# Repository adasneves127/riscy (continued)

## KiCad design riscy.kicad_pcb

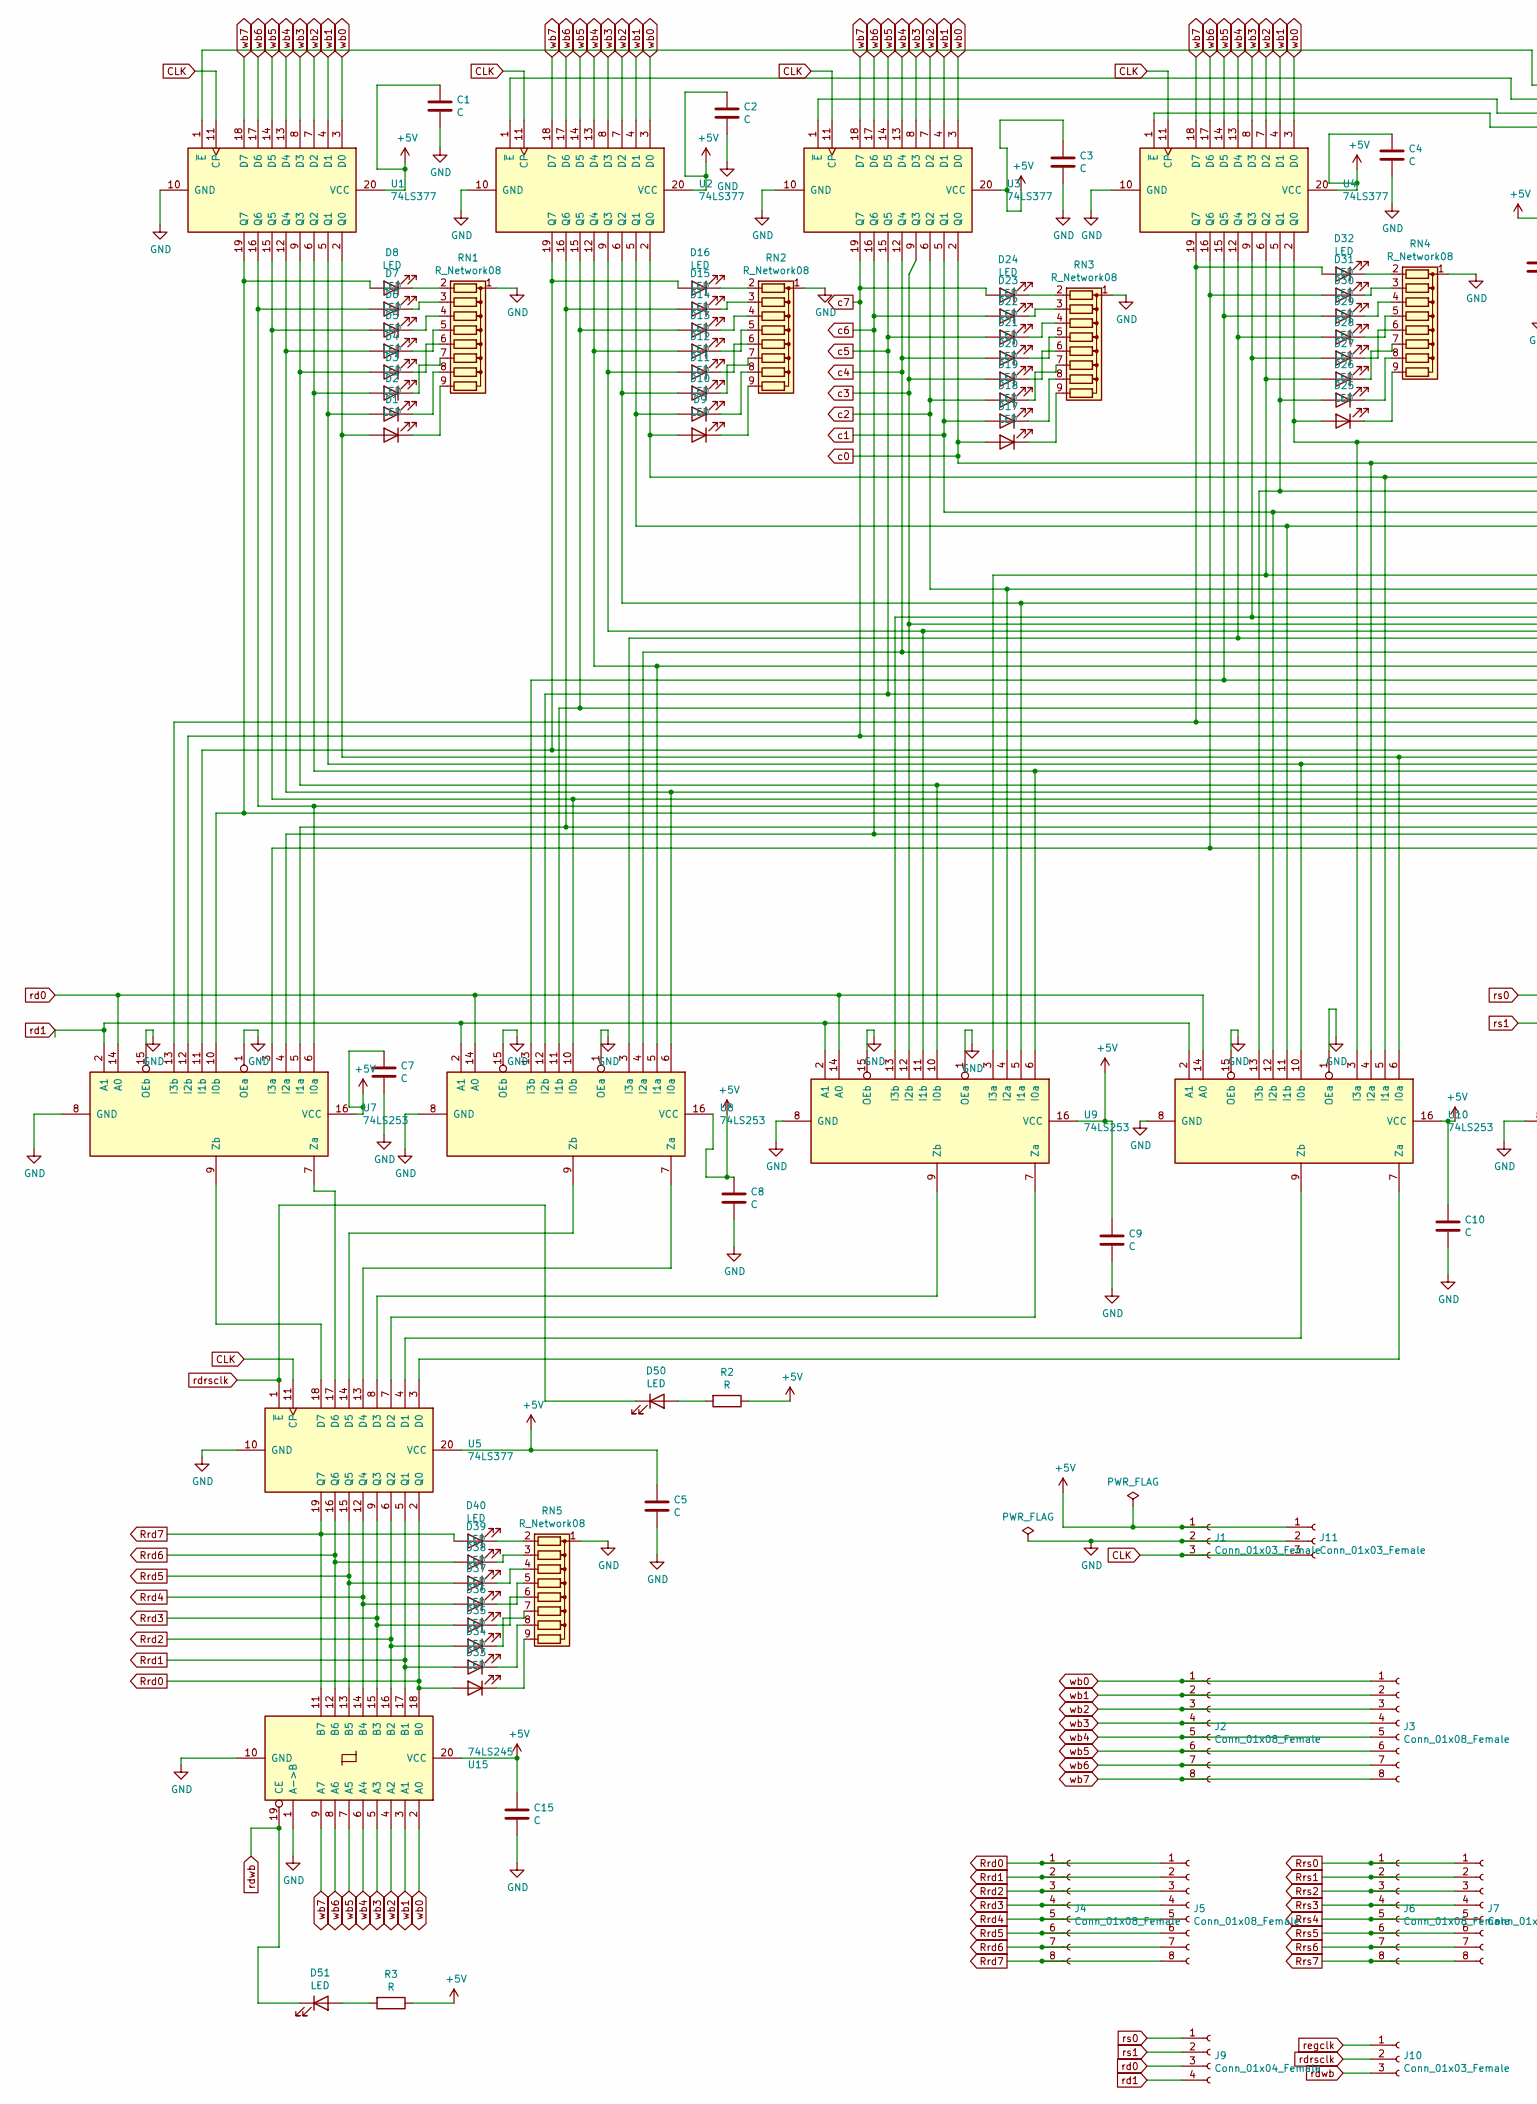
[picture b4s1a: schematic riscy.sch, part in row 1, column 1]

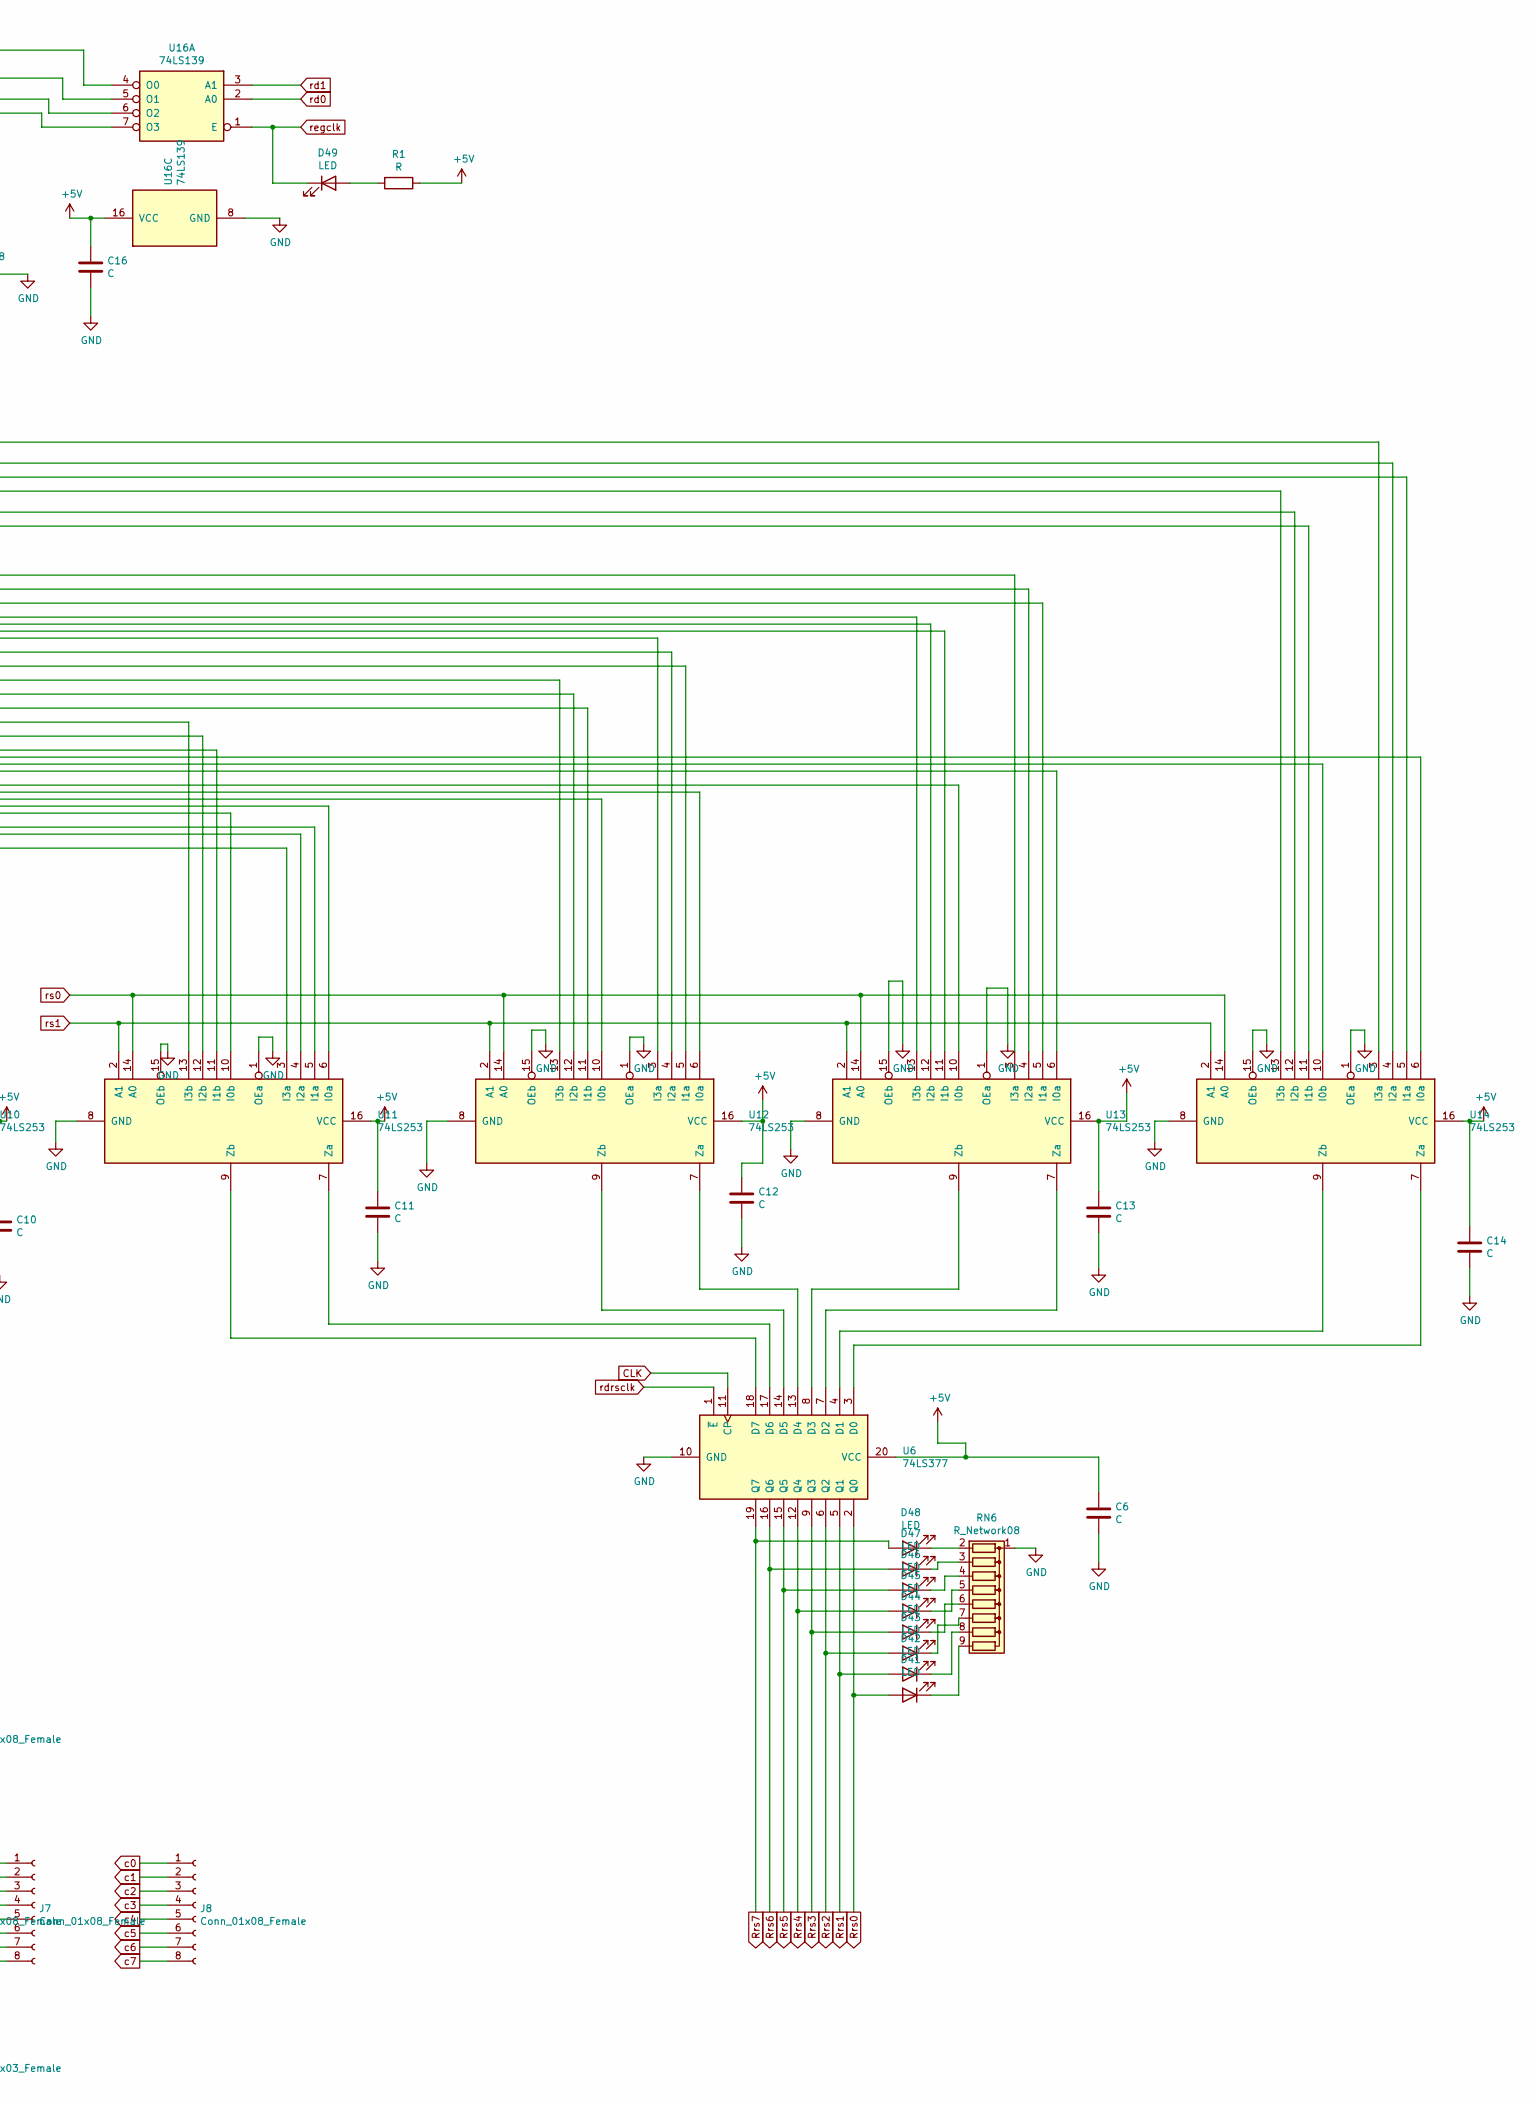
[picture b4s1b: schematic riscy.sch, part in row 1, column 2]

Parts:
C1, C2, C3, C4, C5, C6, C7, C8, C9, C10, C11, C12, C13, C14, C15, C16: C; C_Disc_D3.0mm_W2.0mm_P2.50mm
D1, D2, D3, D4, D5, D6, D7, D8, D9, D10, D11, D12, D13, D14, D15, D16, D17, D18, D19, D20, D21, D22, D23, D24, D25, D26, D27, D28, D29, D30, D31, D32, D33, D34, D35, D36, D37, D38, D39, D40, D41, D42, D43, D44, D45, D46, D47, D48, D49, D50, D51: LED; LED_D5.0mm
J1, J10, J11: Conn_01x03_Female; PinHeader_1x03_P2.54mm_Vertical
J2, J3, J4, J5, J6, J7, J8: Conn_01x08_Female; PinHeader_1x08_P2.54mm_Vertical
J9: Conn_01x04_Female; PinHeader_1x04_P2.54mm_Vertical
R1, R2, R3: R; R_Axial_DIN0204_L3.6mm_D1.6mm_P2.54mm_Vertical
RN1, RN2, RN3, RN4, RN5, RN6: R_Network08; R_Array_SIP9
U1, U2, U3, U4, U5, U6: 74LS377; DIP-20_W7.62mm
U7, U8, U9, U10, U11, U12, U13, U14: 74LS253; DIP-16_W7.62mm
U15: 74LS245; DIP-20_W7.62mm
U16: 74LS139; DIP-16_W7.62mm

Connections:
+5V: C1.1, C2.1, C3.1, C4.1, C5.1, C6.1, C7.1, C8.1, C9.1, C10.1, C11.1, C12.1, C13.1, C14.1, C15.1, C16.1, J1.1, J11.1, R1.1, R2.1, R3.1, U1.20 (VCC), U2.20 (VCC), U3.20 (VCC), U4.20 (VCC), U5.20 (VCC), U6.20 (VCC), U7.16 (VCC), U8.16 (VCC), U9.16 (VCC), U10.16 (VCC), U11.16 (VCC), U12.16 (VCC), U13.16 (VCC), U14.16 (VCC), U15.20 (VCC), U16.16 (VCC)
CLK: J1.3, J11.3, U1.11 (CP), U2.11 (CP), U3.11 (CP), U4.11 (CP), U5.11 (CP), U6.11 (CP)
GND: C1.2, C2.2, C3.2, C4.2, C5.2, C6.2, C7.2, C8.2, C9.2, C10.2, C11.2, C12.2, C13.2, C14.2, C15.2, C16.2, J1.2, J11.2, RN1.1 (common), RN2.1 (common), RN3.1 (common), RN4.1 (common), RN5.1 (common), RN6.1 (common), U1.10 (GND), U2.10 (GND), U3.10 (GND), U4.10 (GND), U5.10 (GND), U6.10 (GND), U7.1 (OEa), U7.8 (GND), U7.15 (OEb), U8.1 (OEa), U8.8 (GND), U8.15 (OEb), U9.1 (OEa), U9.8 (GND), U9.15 (OEb), U10.1 (OEa), U10.8 (GND), U10.15 (OEb), U11.1 (OEa), U11.8 (GND), U11.15 (OEb), U12.1 (OEa), U12.8 (GND), U12.15 (OEb), U13.1 (OEa), U13.8 (GND), U13.15 (OEb), U14.1 (OEa), U14.8 (GND), U14.15 (OEb), U15.1 (A->B), U15.10 (GND), U16.8 (GND)
unnamed: D1.1 (K), RN1.9 (R8)
unnamed: D1.2 (A), U1.2 (Q0), U10.6 (I0a), U14.6 (I0a)
unnamed: D2.1 (K), RN1.8 (R7)
unnamed: D2.2 (A), U1.5 (Q1), U10.10 (I0b), U14.10 (I0b)
unnamed: D3.1 (K), RN1.7 (R6)
unnamed: D3.2 (A), U1.6 (Q2), U9.6 (I0a), U13.6 (I0a)
unnamed: D4.1 (K), RN1.6 (R5)
unnamed: D4.2 (A), U1.9 (Q3), U9.10 (I0b), U13.10 (I0b)
unnamed: D5.1 (K), RN1.5 (R4)
unnamed: D5.2 (A), U1.12 (Q4), U8.6 (I0a), U12.6 (I0a)
unnamed: D6.1 (K), RN1.4 (R3)
unnamed: D6.2 (A), U1.15 (Q5), U8.10 (I0b), U12.10 (I0b)
unnamed: D7.1 (K), RN1.3 (R2)
unnamed: D7.2 (A), U1.16 (Q6), U7.6 (I0a), U11.6 (I0a)
unnamed: D8.1 (K), RN1.2 (R1)
unnamed: D8.2 (A), U1.19 (Q7), U7.10 (I0b), U11.10 (I0b)
unnamed: D9.1 (K), RN2.9 (R8)
unnamed: D9.2 (A), U2.2 (Q0), U10.5 (I1a), U14.5 (I1a)
unnamed: D10.1 (K), RN2.8 (R7)
unnamed: D10.2 (A), U2.5 (Q1), U10.11 (I1b), U14.11 (I1b)
unnamed: D11.1 (K), RN2.7 (R6)
unnamed: D11.2 (A), U2.6 (Q2), U9.5 (I1a), U13.5 (I1a)
unnamed: D12.1 (K), RN2.6 (R5)
unnamed: D12.2 (A), U2.9 (Q3), U9.11 (I1b), U13.11 (I1b)
unnamed: D13.1 (K), RN2.5 (R4)
unnamed: D13.2 (A), U2.12 (Q4), U8.5 (I1a), U12.5 (I1a)
unnamed: D14.1 (K), RN2.4 (R3)
unnamed: D14.2 (A), U2.15 (Q5), U8.11 (I1b), U12.11 (I1b)
unnamed: D15.1 (K), RN2.3 (R2)
unnamed: D15.2 (A), U2.16 (Q6), U7.5 (I1a), U11.5 (I1a)
unnamed: D16.1 (K), RN2.2 (R1)
unnamed: D16.2 (A), U2.19 (Q7), U7.11 (I1b), U11.11 (I1b)
unnamed: D17.1 (K), RN3.9 (R8)
unnamed: D18.1 (K), RN3.8 (R7)
unnamed: D19.1 (K), RN3.7 (R6)
unnamed: D20.1 (K), RN3.6 (R5)
unnamed: D21.1 (K), RN3.5 (R4)
unnamed: D22.1 (K), RN3.4 (R3)
unnamed: D23.1 (K), RN3.3 (R2)
unnamed: D24.1 (K), RN3.2 (R1)
unnamed: D25.1 (K), RN4.9 (R8)
unnamed: D25.2 (A), U4.2 (Q0), U10.3 (I3a), U14.3 (I3a)
unnamed: D26.1 (K), RN4.8 (R7)
unnamed: D26.2 (A), U4.5 (Q1), U10.13 (I3b), U14.13 (I3b)
unnamed: D27.1 (K), RN4.7 (R6)
unnamed: D27.2 (A), U4.6 (Q2), U9.3 (I3a), U13.3 (I3a)
unnamed: D28.1 (K), RN4.6 (R5)
unnamed: D28.2 (A), U4.9 (Q3), U9.13 (I3b), U13.13 (I3b)
unnamed: D29.1 (K), RN4.5 (R4)
unnamed: D29.2 (A), U4.12 (Q4), U8.3 (I3a), U12.3 (I3a)
unnamed: D30.1 (K), RN4.4 (R3)
unnamed: D30.2 (A), U4.15 (Q5), U8.13 (I3b), U12.13 (I3b)
unnamed: D31.1 (K), RN4.3 (R2)
unnamed: D31.2 (A), U4.16 (Q6), U7.3 (I3a), U11.3 (I3a)
unnamed: D32.1 (K), RN4.2 (R1)
unnamed: D32.2 (A), U4.19 (Q7), U7.13 (I3b), U11.13 (I3b)
unnamed: D33.1 (K), RN5.9 (R8)
unnamed: D34.1 (K), RN5.8 (R7)
unnamed: D35.1 (K), RN5.7 (R6)
unnamed: D36.1 (K), RN5.6 (R5)
unnamed: D37.1 (K), RN5.5 (R4)
unnamed: D38.1 (K), RN5.4 (R3)
unnamed: D39.1 (K), RN5.3 (R2)
unnamed: D40.1 (K), RN5.2 (R1)
unnamed: D41.1 (K), RN6.9 (R8)
unnamed: D42.1 (K), RN6.8 (R7)
unnamed: D43.1 (K), RN6.7 (R6)
unnamed: D44.1 (K), RN6.6 (R5)
unnamed: D45.1 (K), RN6.5 (R4)
unnamed: D46.1 (K), RN6.4 (R3)
unnamed: D47.1 (K), RN6.3 (R2)
unnamed: D48.1 (K), RN6.2 (R1)
unnamed: D49.2 (A), R1.2
unnamed: D50.2 (A), R2.2
unnamed: D51.2 (A), R3.2
unnamed: U1.1 (~E), U16.4 (O0)
unnamed: U5.7 (D2), U9.7 (Za)
unnamed: U5.8 (D3), U9.9 (Zb)
unnamed: U5.13 (D4), U8.7 (Za)
unnamed: U5.14 (D5), U8.9 (Zb)
unnamed: U5.17 (D6), U7.7 (Za)
unnamed: U5.18 (D7), U7.9 (Zb)
unnamed: U5.3 (D0), U10.7 (Za)
unnamed: U5.4 (D1), U10.9 (Zb)
unnamed: U6.17 (D6), U11.7 (Za)
unnamed: U6.18 (D7), U11.9 (Zb)
unnamed: U6.13 (D4), U12.7 (Za)
unnamed: U6.14 (D5), U12.9 (Zb)
unnamed: U6.7 (D2), U13.7 (Za)
unnamed: U6.8 (D3), U13.9 (Zb)
unnamed: U6.3 (D0), U14.7 (Za)
unnamed: U6.4 (D1), U14.9 (Zb)
unnamed: U2.1 (~E), U16.5 (O1)
unnamed: U3.1 (~E), U16.6 (O2)
unnamed: U4.1 (~E), U16.7 (O3)
Rrd0: D33.2 (A), J4.1, J5.1, U5.2 (Q0), U15.18 (B0)
Rrd1: D34.2 (A), J4.2, J5.2, U5.5 (Q1), U15.17 (B1)
Rrd2: D35.2 (A), J4.3, J5.3, U5.6 (Q2), U15.16 (B2)
Rrd3: D36.2 (A), J4.4, J5.4, U5.9 (Q3), U15.15 (B3)
Rrd4: D37.2 (A), J4.5, J5.5, U5.12 (Q4), U15.14 (B4)
Rrd5: D38.2 (A), J4.6, J5.6, U5.15 (Q5), U15.13 (B5)
Rrd6: D39.2 (A), J4.7, J5.7, U5.16 (Q6), U15.12 (B6)
Rrd7: D40.2 (A), J4.8, J5.8, U5.19 (Q7), U15.11 (B7)
Rrs0: D41.2 (A), J6.1, J7.1, U6.2 (Q0)
Rrs1: D42.2 (A), J6.2, J7.2, U6.5 (Q1)
Rrs2: D43.2 (A), J6.3, J7.3, U6.6 (Q2)
Rrs3: D44.2 (A), J6.4, J7.4, U6.9 (Q3)
Rrs4: D45.2 (A), J6.5, J7.5, U6.12 (Q4)
Rrs5: D46.2 (A), J6.6, J7.6, U6.15 (Q5)
Rrs6: D47.2 (A), J6.7, J7.7, U6.16 (Q6)
Rrs7: D48.2 (A), J6.8, J7.8, U6.19 (Q7)
c0: D17.2 (A), J8.1, U3.2 (Q0), U10.4 (I2a), U14.4 (I2a)
c1: D18.2 (A), J8.2, U3.5 (Q1), U10.12 (I2b), U14.12 (I2b)
c2: D19.2 (A), J8.3, U3.6 (Q2), U9.4 (I2a), U13.4 (I2a)
c3: D20.2 (A), J8.4, U3.9 (Q3), U9.12 (I2b), U13.12 (I2b)
c4: D21.2 (A), J8.5, U3.12 (Q4), U8.4 (I2a), U12.4 (I2a)
c5: D22.2 (A), J8.6, U3.15 (Q5), U8.12 (I2b), U12.12 (I2b)
c6: D23.2 (A), J8.7, U3.16 (Q6), U7.4 (I2a), U11.4 (I2a)
c7: D24.2 (A), J8.8, U3.19 (Q7), U7.12 (I2b), U11.12 (I2b)
rd0: J9.3, U7.14 (A0), U8.14 (A0), U9.14 (A0), U10.14 (A0), U16.2 (A0)
rd1: J9.4, U7.2 (A1), U8.2 (A1), U9.2 (A1), U10.2 (A1), U16.3 (A1)
rdrsclk: D50.1 (K), J10.2, U5.1 (~E), U6.1 (~E)
rdwb: D51.1 (K), J10.3, U15.19 (CE)
regclk: D49.1 (K), J10.1, U16.1 (E)
wb0: J2.1, J3.1, U1.3 (D0), U2.3 (D0), U3.3 (D0), U4.3 (D0), U15.2 (A0)
wb1: J2.2, J3.2, U1.4 (D1), U2.4 (D1), U3.4 (D1), U4.4 (D1), U15.3 (A1)
wb2: J2.3, J3.3, U1.7 (D2), U2.7 (D2), U3.7 (D2), U4.7 (D2), U15.4 (A2)
wb3: J2.4, J3.4, U1.8 (D3), U2.8 (D3), U3.8 (D3), U4.8 (D3), U15.5 (A3)
wb4: J2.5, J3.5, U1.13 (D4), U2.13 (D4), U3.13 (D4), U4.13 (D4), U15.6 (A4)
wb5: J2.6, J3.6, U1.14 (D5), U2.14 (D5), U3.14 (D5), U4.14 (D5), U15.7 (A5)
wb6: J2.7, J3.7, U1.17 (D6), U2.17 (D6), U3.17 (D6), U4.17 (D6), U15.8 (A6)
wb7: J2.8, J3.8, U1.18 (D7), U2.18 (D7), U3.18 (D7), U4.18 (D7), U15.9 (A7)

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
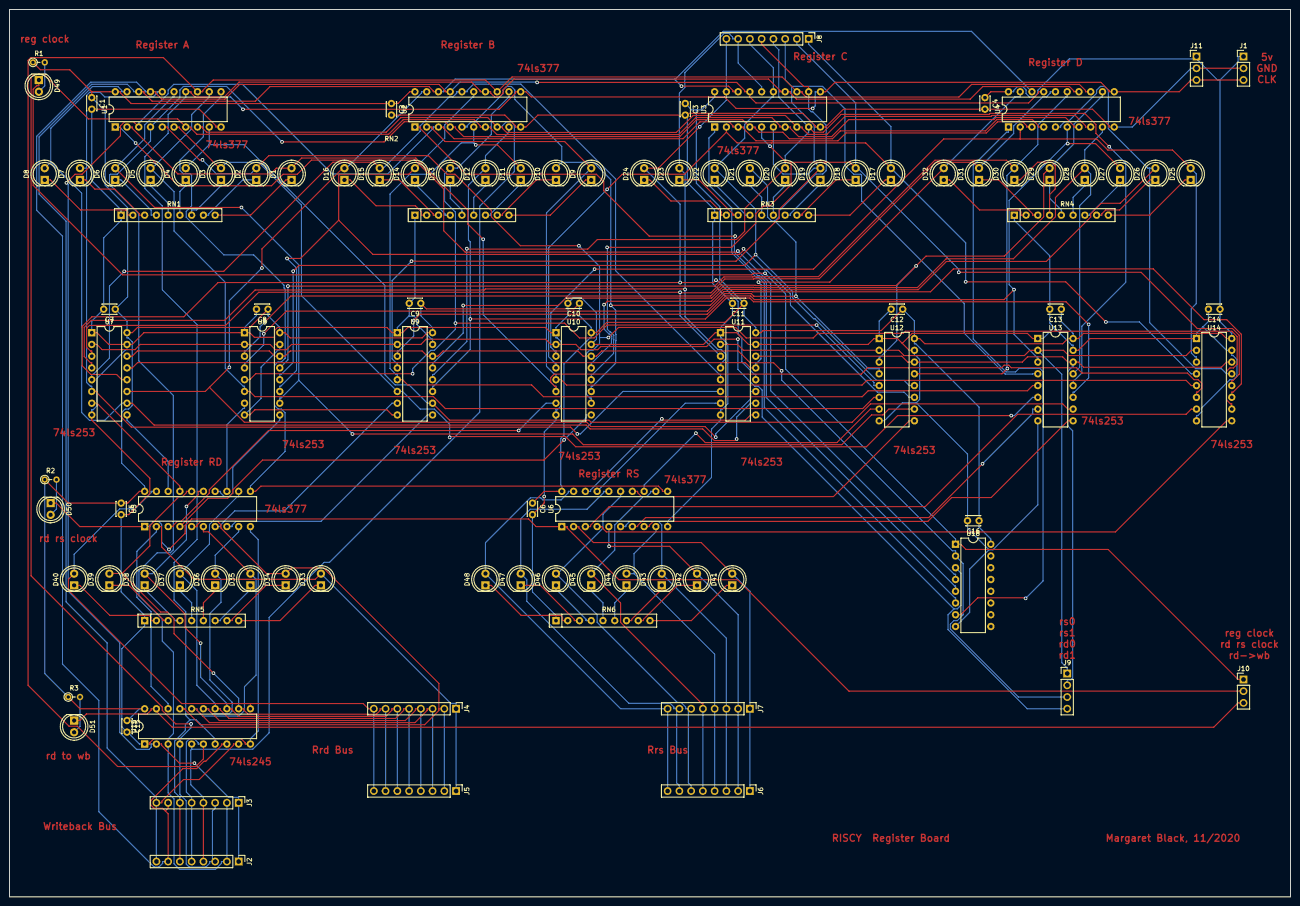
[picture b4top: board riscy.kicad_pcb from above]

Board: 2 copper layers, 276.9 x 191.8 mm, 103 parts (0 on the bottom side), 137 nets.

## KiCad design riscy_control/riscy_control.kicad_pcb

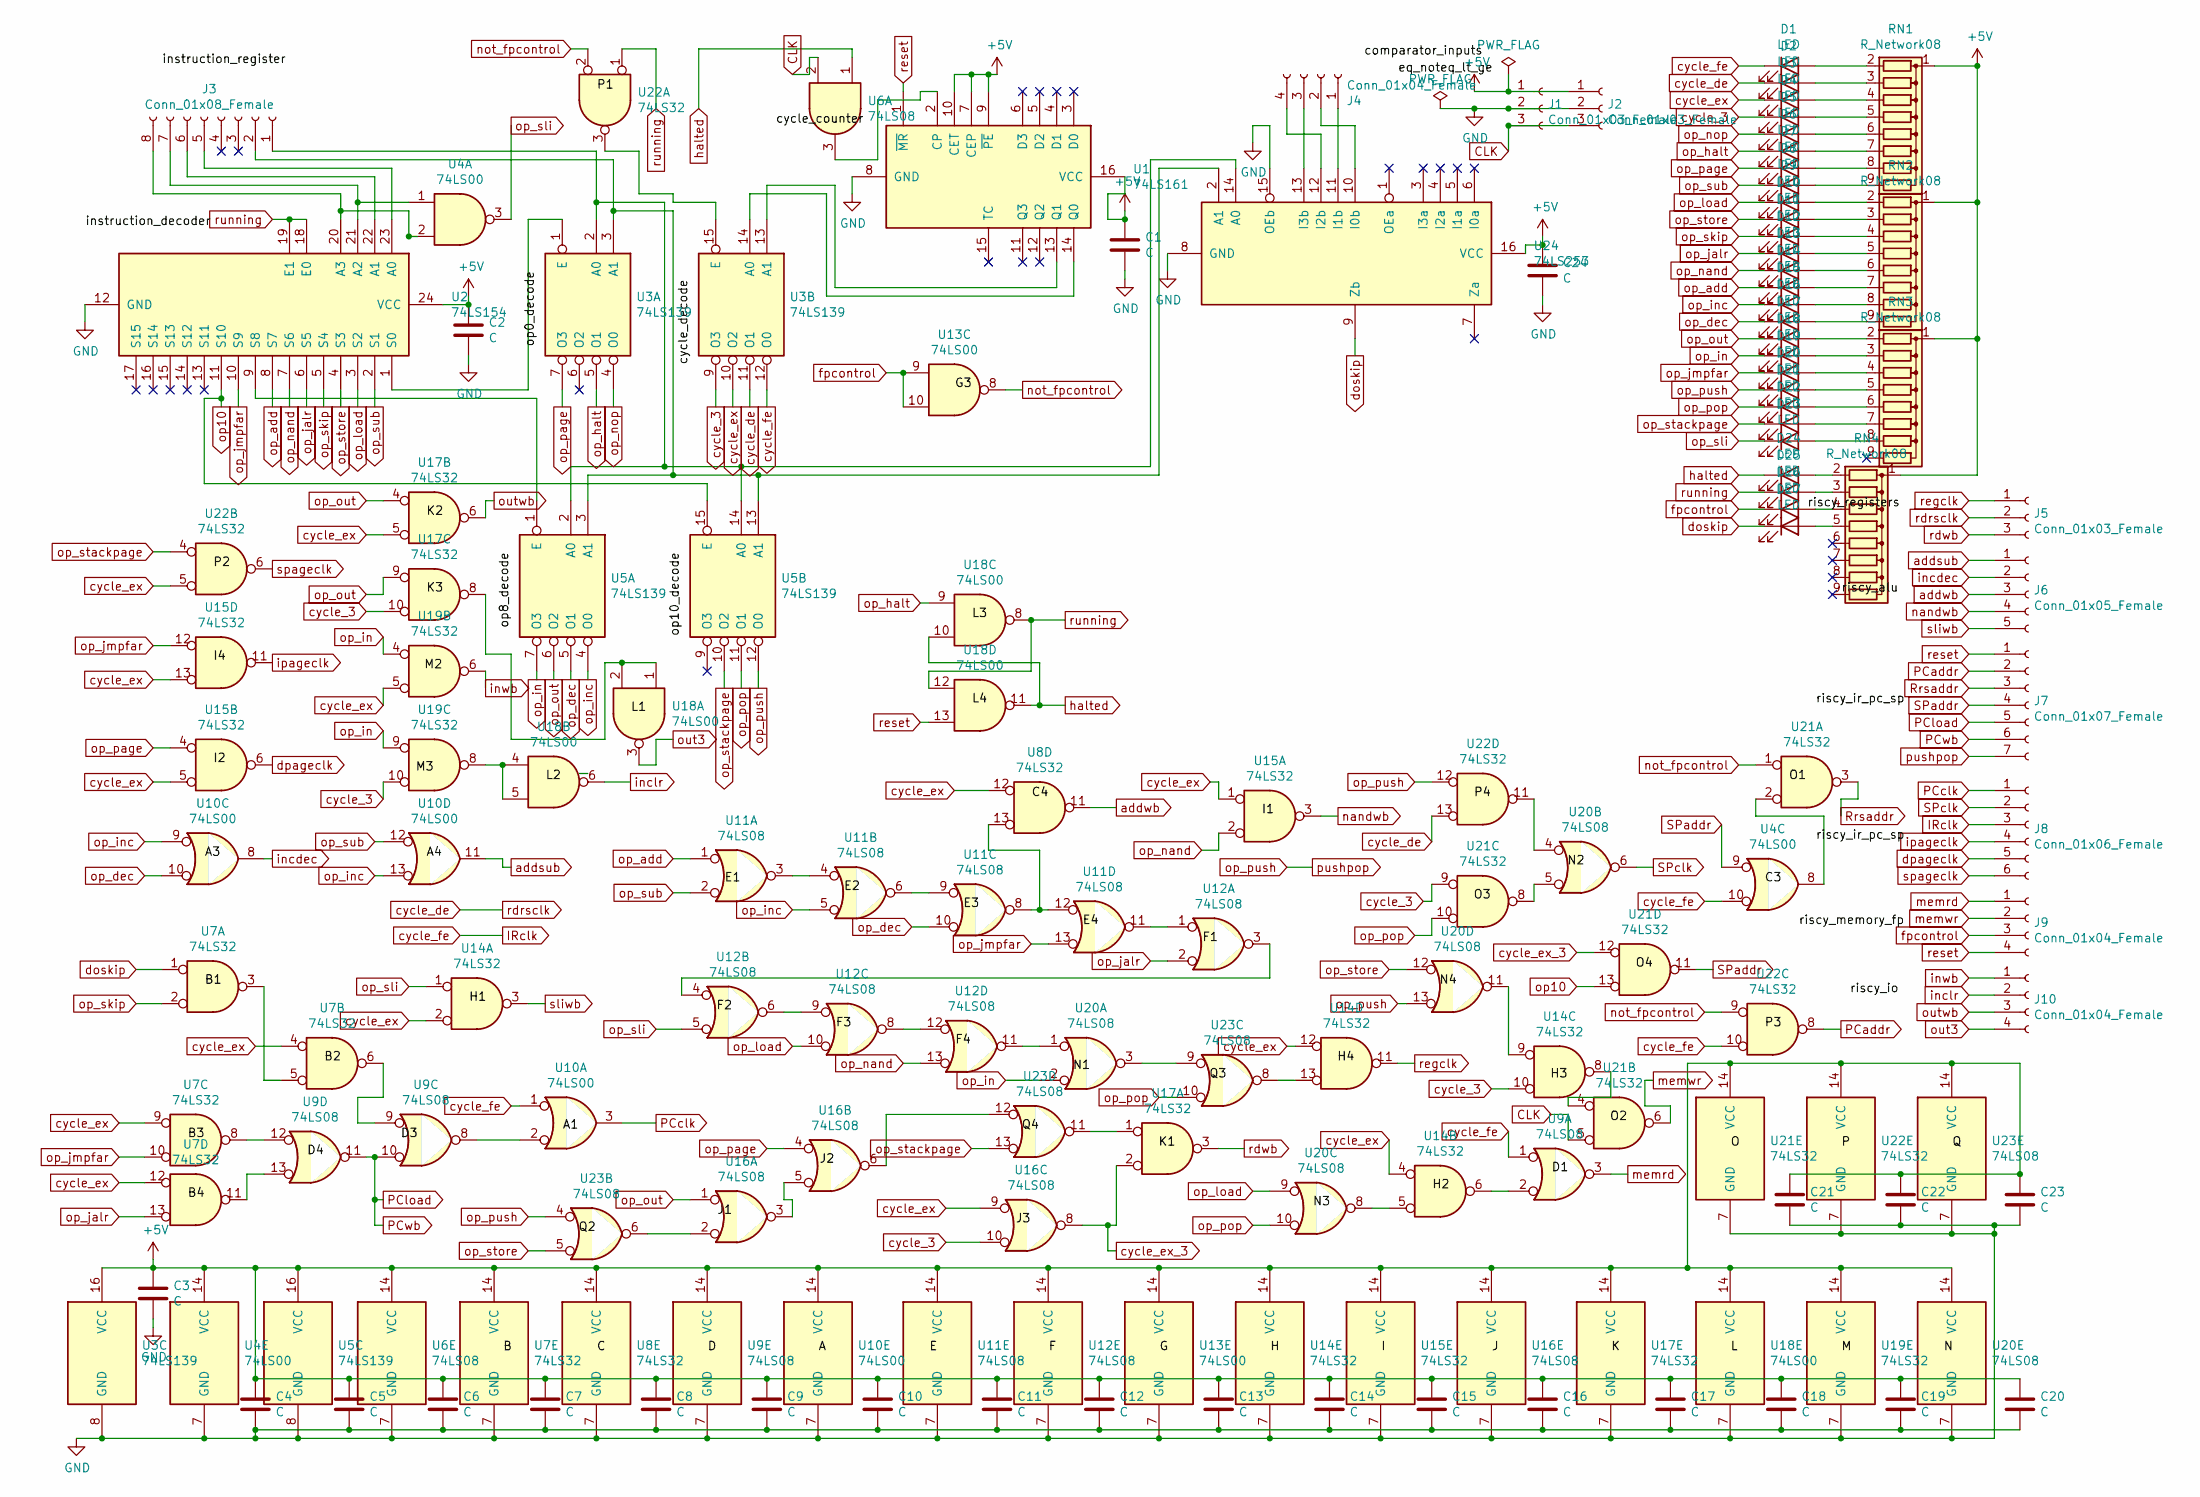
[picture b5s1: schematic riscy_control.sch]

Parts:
C1, C2, C3, C4, C5, C6, C7, C8, C9, C10, C11, C12, C13, C14, C15, C16, C17, C18, C19, C20, C21, C22, C23, C24: C; C_Disc_D3.0mm_W2.0mm_P2.50mm
D1, D2, D3, D4, D5, D6, D7, D8, D9, D10, D11, D12, D13, D14, D15, D16, D17, D18, D19, D20, D21, D22, D23, D24, D25, D26, D27: LED; LED_D5.0mm
J1, J2, J5: Conn_01x03_Female; PinSocket_1x03_P2.54mm_Vertical
J3: Conn_01x08_Female; PinSocket_1x08_P2.54mm_Vertical
J4, J10: Conn_01x04_Female; PinSocket_1x04_P2.54mm_Vertical
J6: Conn_01x05_Female; PinSocket_1x05_P2.54mm_Vertical
J7: Conn_01x07_Female; PinSocket_1x07_P2.54mm_Vertical
J8: Conn_01x06_Female; PinSocket_1x06_P2.54mm_Vertical
J9: Conn_01x04_Female; PinHeader_1x04_P2.54mm_Vertical
RN1, RN2, RN3, RN4: R_Network08; R_Array_SIP9
U1: 74LS161; DIP-16_W7.62mm
U2: 74LS154; DIP-24_W15.24mm
U3, U5: 74LS139; DIP-16_W7.62mm
U4, U10, U13, U18: 74LS00; DIP-14_W7.62mm
U6, U9, U11, U12, U16, U20, U23: 74LS08; DIP-14_W7.62mm
U7, U8, U14, U15, U17, U19, U21, U22: 74LS32; DIP-14_W7.62mm
U24: 74LS253; DIP-16_W7.62mm

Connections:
+5V: C1.1, C2.1, C3.1, C4.1, C5.1, C6.1, C7.1, C8.1, C9.1, C10.1, C11.1, C12.1, C13.1, C14.1, C15.1, C16.1, C17.1, C18.1, C19.1, C20.1, C21.1, C22.1, C23.1, C24.1, J1.1, J2.1, RN1.1 (common), RN2.1 (common), RN3.1 (common), RN4.1 (common), U1.7 (CEP), U1.9 (~PE), U1.10 (CET), U1.16 (VCC), U2.24 (VCC), U3.16 (VCC), U4.14 (VCC), U5.16 (VCC), U6.14 (VCC), U7.14 (VCC), U8.14 (VCC), U9.14 (VCC), U10.14 (VCC), U11.14 (VCC), U12.14 (VCC), U13.14 (VCC), U14.14 (VCC), U15.14 (VCC), U16.14 (VCC), U17.14 (VCC), U18.14 (VCC), U19.14 (VCC), U20.14 (VCC), U21.14 (VCC), U22.14 (VCC), U23.14 (VCC), U24.16 (VCC)
CLK: J1.3, J2.3, U6.2, U21.5
GND: C1.2, C2.2, C3.2, C4.2, C5.2, C6.2, C7.2, C8.2, C9.2, C10.2, C11.2, C12.2, C13.2, C14.2, C15.2, C16.2, C17.2, C18.2, C19.2, C20.2, C21.2, C22.2, C23.2, C24.2, J1.2, J2.2, U1.8 (GND), U2.12 (GND), U3.8 (GND), U4.7 (GND), U5.8 (GND), U6.7 (GND), U7.7 (GND), U8.7 (GND), U9.7 (GND), U10.7 (GND), U11.7 (GND), U12.7 (GND), U13.7 (GND), U14.7 (GND), U15.7 (GND), U16.7 (GND), U17.7 (GND), U18.7 (GND), U19.7 (GND), U20.7 (GND), U21.7 (GND), U22.7 (GND), U23.7 (GND), U24.8 (GND), U24.15 (OEb)
IRclk: D1.1 (K), J8.3, U3.12 (O0), U4.10, U9.1, U10.1, U22.10
unnamed: D1.2 (A), RN1.2 (R1)
unnamed: D2.2 (A), RN1.3 (R2)
unnamed: D3.2 (A), RN1.4 (R3)
unnamed: D4.2 (A), RN1.5 (R4)
unnamed: D5.2 (A), RN1.6 (R5)
unnamed: D6.2 (A), RN1.7 (R6)
unnamed: D7.2 (A), RN1.8 (R7)
unnamed: D8.2 (A), RN1.9 (R8)
unnamed: D9.2 (A), RN2.2 (R1)
unnamed: D10.2 (A), RN2.3 (R2)
unnamed: D11.2 (A), RN2.4 (R3)
unnamed: D12.2 (A), RN2.5 (R4)
unnamed: D13.2 (A), RN2.6 (R5)
unnamed: D14.2 (A), RN2.7 (R6)
unnamed: D15.2 (A), RN2.8 (R7)
unnamed: D16.2 (A), RN2.9 (R8)
unnamed: D17.2 (A), RN3.2 (R1)
unnamed: D18.2 (A), RN3.3 (R2)
unnamed: D19.2 (A), RN3.4 (R3)
unnamed: D20.2 (A), RN3.5 (R4)
unnamed: D21.2 (A), RN3.6 (R5)
unnamed: D22.2 (A), RN3.7 (R6)
unnamed: D23.2 (A), RN3.8 (R7)
unnamed: D24.2 (A), RN4.2 (R1)
unnamed: D25.2 (A), RN4.3 (R2)
unnamed: D26.2 (A), RN4.4 (R3)
unnamed: D27.2 (A), RN4.5 (R4)
unnamed: J3.1, U3.2 (A0), U5.2 (A0), U5.14 (A0), U24.14 (A0)
unnamed: J3.2, U3.3 (A1), U5.3 (A1), U5.13 (A1), U24.2 (A1)
unnamed: J3.5, U2.23 (A0)
unnamed: J3.6, U2.22 (A1)
unnamed: J3.7, U2.21 (A2), U4.1
unnamed: J3.8, U2.20 (A3), U4.2
unnamed: J4.1, U24.11 (I1b)
unnamed: J4.2, U24.10 (I0b)
unnamed: J4.3, U24.13 (I3b)
unnamed: J4.4, U24.12 (I2b)
unnamed: U1.2 (CP), U6.3
unnamed: U1.13 (Q1), U3.13 (A1)
unnamed: U1.14 (Q0), U3.14 (A0)
unnamed: U2.1 (S0), U3.1 (E)
unnamed: U2.9 (S8), U5.1 (E)
unnamed: U7.3, U7.5
unnamed: U7.6, U9.9
unnamed: U7.8, U9.12
unnamed: U7.11, U9.13
unnamed: U9.8, U10.2
unnamed: U11.3, U11.4
unnamed: U11.6, U11.9
unnamed: U11.11, U12.1
unnamed: U8.13, U11.8, U11.12
unnamed: U12.3, U12.4
unnamed: U12.6, U12.9
unnamed: U12.11, U20.1
unnamed: U12.8, U12.12
unnamed: U14.5, U20.8
unnamed: U9.2, U14.6
unnamed: U14.8, U21.4
unnamed: U14.9, U20.11
unnamed: U14.13, U23.8
unnamed: U16.2, U23.6
unnamed: U16.3, U16.5
unnamed: U16.6, U23.12
unnamed: U17.1, U23.11
unnamed: U17.8, U18.1, U18.2
unnamed: U18.4, U18.5, U19.8
unnamed: U20.3, U23.9
unnamed: U20.4, U22.11
unnamed: U20.5, U21.8
unnamed: U4.8, U21.2
unnamed: U3.15 (E), U22.3
PCaddr: J7.2, U22.8
PCclk: J8.1, U10.3
PCload: J7.5, J7.6, U9.10, U9.11
Rrsaddr: J7.3, U21.3
SPaddr: J7.4, U4.9, U21.11
SPclk: J8.2, U20.6
addsub: J6.1, U10.11
addwb: J6.3, U8.11
cycle_3: D4.1 (K), U3.9 (O3), U14.10, U16.10, U17.10, U19.10, U21.9
cycle_de: D2.1 (K), J5.2, U3.11 (O1), U22.13
cycle_ex: D3.1 (K), U3.10 (O2), U7.4, U7.9, U7.12, U8.12, U14.2, U14.4, U14.12, U15.1, U15.5, U15.13, U16.9, U17.5, U19.5, U22.5
cycle_ex_3: U16.8, U17.2, U21.12
doskip: D27.1 (K), U7.1, U24.9 (Zb)
dpageclk: J8.5, U15.6
fpcontrol: D26.1 (K), J9.3, U13.9, U13.10
halted: D24.1 (K), U6.1, U18.10, U18.11
incdec: J6.2, U10.8
inclr: J10.2, U18.6
inwb: J10.1, U19.6
ipageclk: J8.4, U15.11
memrd: J9.1, U9.3
memwr: J9.2, U21.6
nandwb: J6.4, U15.3
not_fpcontrol: U13.8, U21.1, U22.2, U22.9
op10: U2.11 (S10), U5.15 (E), U21.13
op_add: D14.1 (K), U2.8 (S7), U11.1
op_dec: D16.1 (K), U5.5 (O1), U10.10, U11.10
op_halt: D6.1 (K), U3.5 (O1), U18.9
op_in: D18.1 (K), U5.7 (O3), U19.4, U19.9, U20.2
op_inc: D15.1 (K), U5.4 (O0), U10.9, U10.13, U11.5
op_jalr: D12.1 (K), U2.6 (S5), U7.13, U12.2
op_jmpfar: D19.1 (K), U2.10 (S9), U7.10, U11.13, U15.12
op_load: D9.1 (K), U2.3 (S2), U12.10, U20.9
op_nand: D13.1 (K), U2.7 (S6), U12.13, U15.2
op_nop: D5.1 (K), U3.4 (O0)
op_out: D17.1 (K), U5.6 (O2), U16.1, U17.4, U17.9
op_page: D7.1 (K), U3.7 (O3), U15.4, U16.4
op_pop: D21.1 (K), U5.11 (O1), U20.10, U21.10, U23.10
op_push: D20.1 (K), J7.7, U5.12 (O0), U20.13, U22.12, U23.4
op_skip: D11.1 (K), U2.5 (S4), U7.2
op_sli: D23.1 (K), U4.3, U12.5, U14.1
op_stackpage: D22.1 (K), U5.10 (O2), U22.4, U23.13
op_store: D10.1 (K), U2.4 (S3), U20.12, U23.5
op_sub: D8.1 (K), U2.2 (S1), U10.12, U11.2
out3: J10.4, U18.3
outwb: J10.3, U17.6
rdwb: J5.3, U17.3
regclk: J5.1, U14.11
reset: J7.1, J9.4, U1.1 (~MR), U18.13
running: D25.1 (K), U2.18 (E0), U2.19 (E1), U18.8, U18.12, U22.1
sliwb: J6.5, U14.3
spageclk: J8.6, U22.6

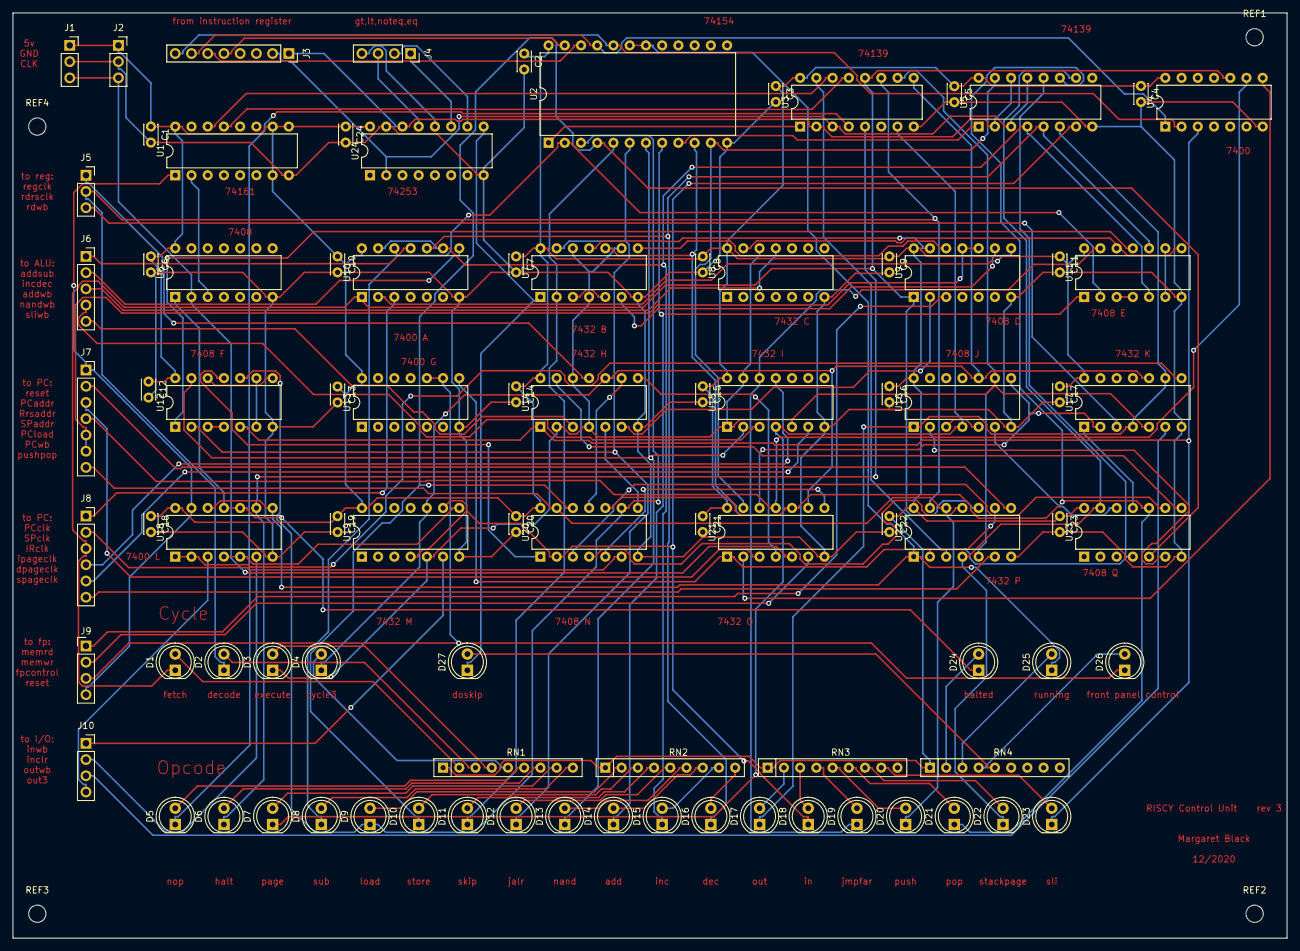
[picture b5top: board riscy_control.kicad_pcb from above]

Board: 2 copper layers, 199.4 x 144.8 mm, 93 parts (0 on the bottom side), 127 nets.

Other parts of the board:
REF1, REF2, REF3, REF4: MountingHole_2.7mm_M2.5

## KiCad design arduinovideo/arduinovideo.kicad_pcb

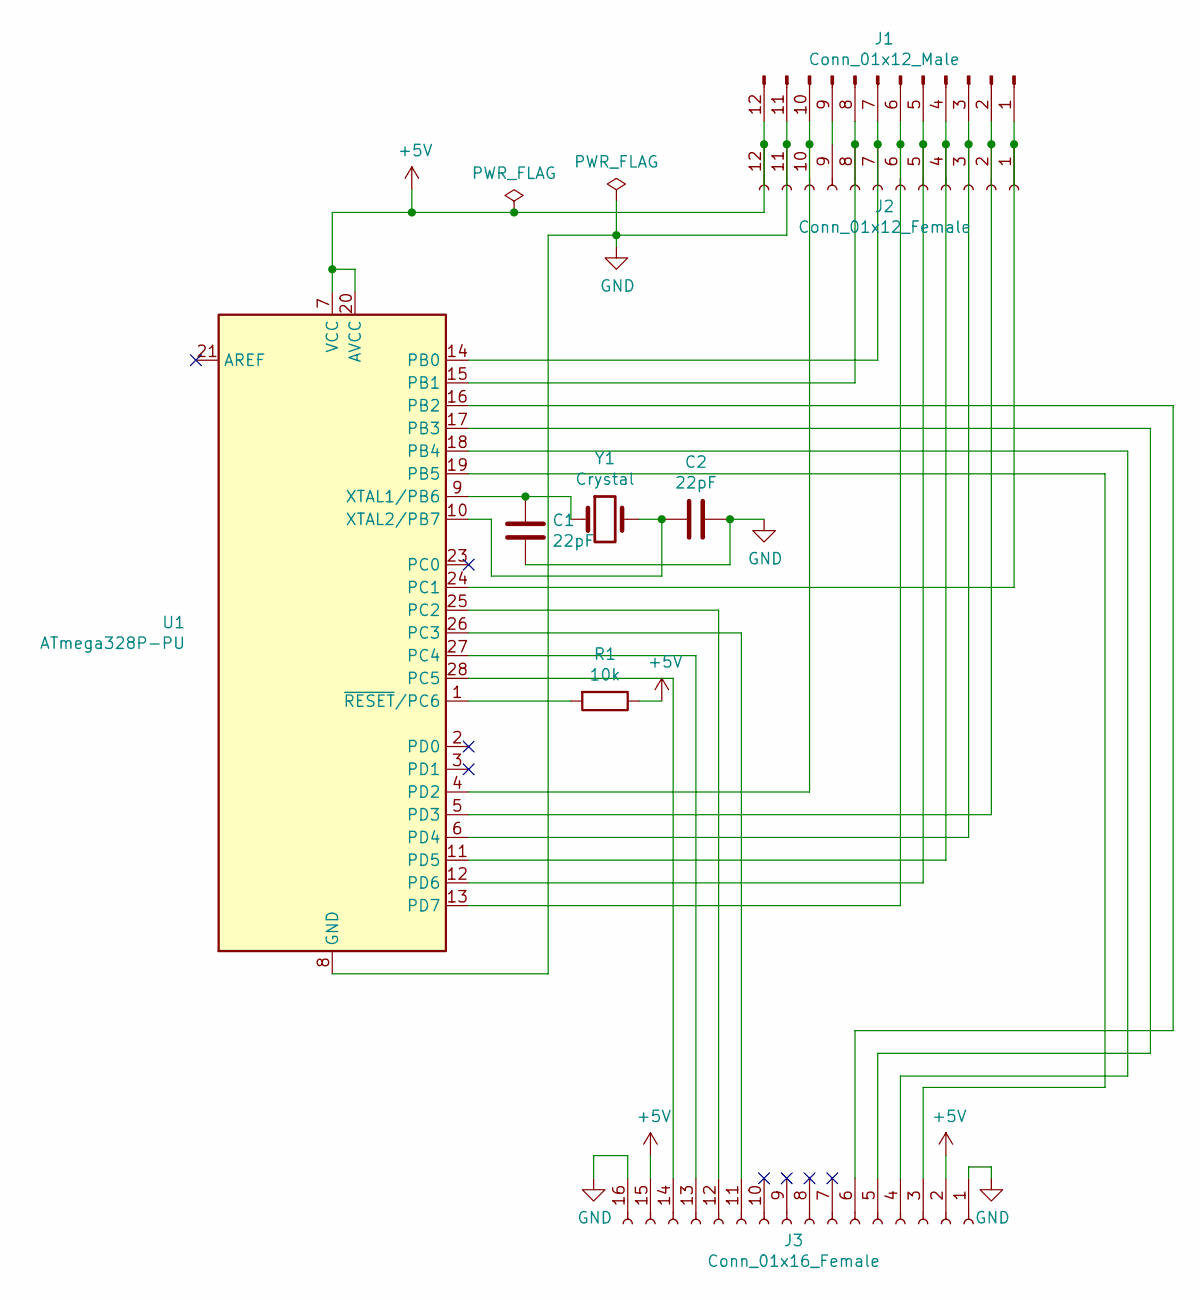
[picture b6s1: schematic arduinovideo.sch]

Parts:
C1, C2: 22pF; C_Disc_D4.7mm_W2.5mm_P5.00mm
J1: Conn_01x12_Male; PinHeader_1x12_P2.54mm_Vertical
J2: Conn_01x12_Female; PinHeader_1x12_P2.54mm_Vertical
J3: Conn_01x16_Female; PinHeader_1x16_P2.54mm_Vertical
R1: 10k; R_Axial_DIN0207_L6.3mm_D2.5mm_P7.62mm_Horizontal
U1: ATmega328P-PU; DIP-28_W7.62mm
Y1: Crystal; Crystal_HC49-U_Vertical

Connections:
+5V: J1.12, J2.12, J3.2, J3.15, R1.1, U1.7 (VCC), U1.20 (AVCC)
GND: C1.2, C2.1, J1.11, J2.11, J3.1, J3.16, U1.8 (GND), U1.22 (GND)
unnamed: C1.1, U1.9 (XTAL1/PB6), Y1.1
unnamed: C2.2, U1.10 (XTAL2/PB7), Y1.2
unnamed: J1.1, J2.1, U1.24 (PC1)
unnamed: J1.2, J2.2, U1.5 (PD3)
unnamed: J1.3, J2.3, U1.6 (PD4)
unnamed: J1.4, J2.4, U1.11 (PD5)
unnamed: J1.5, J2.5, U1.12 (PD6)
unnamed: J1.6, J2.6, U1.13 (PD7)
unnamed: J1.7, J2.7, U1.14 (PB0)
unnamed: J1.8, J2.8, U1.15 (PB1)
unnamed: J1.9, J2.9
unnamed: J1.10, J2.10, U1.4 (PD2)
unnamed: J3.3, U1.19 (PB5)
unnamed: J3.4, U1.18 (PB4)
unnamed: J3.5, U1.17 (PB3)
unnamed: J3.6, U1.16 (PB2)
unnamed: J3.11, U1.26 (PC3)
unnamed: J3.12, U1.25 (PC2)
unnamed: J3.13, U1.27 (PC4)
unnamed: J3.14, U1.28 (PC5)
unnamed: R1.2, U1.1 (~RESET~/PC6)
